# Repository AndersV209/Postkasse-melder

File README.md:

# Postkasse melder

min version af postkasse melder 

der sidder 2 stk micro switch i postkassen, en på den øverste låge og en på den nederste låge, så den selv resetter når postkassen er tømt.

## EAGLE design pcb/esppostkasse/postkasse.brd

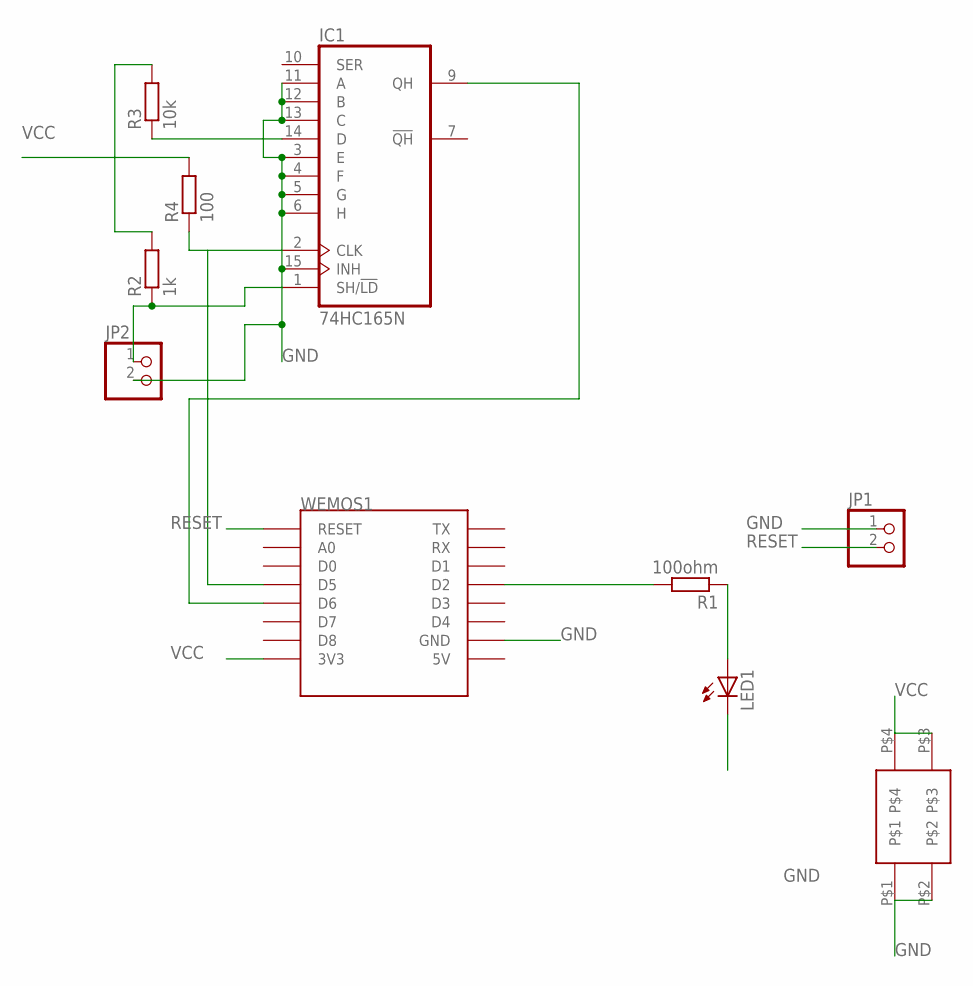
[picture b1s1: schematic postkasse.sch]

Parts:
IC1: 74HC165N; DIL16
JP1, JP2: PINHD-1X2; 1X02
LED1: LED5MM
R1: 100ohm; 0204/7
R2: 1k; 0204/7
R3: 10k; 0204/7
R4: 100; 0204/7
U$1: BAT18650
WEMOS1: WEMOS-D1-MINI

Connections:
GND: IC1.3 (E), IC1.4 (F), IC1.5 (G), IC1.6 (H), IC1.8 (GND), IC1.11 (A), IC1.12 (B), IC1.13 (C), IC1.15 (INH), JP1.1, JP2.2, LED1.K (C), U$1.P$1, U$1.P$2, WEMOS1.GND
unnamed: LED1.A, R1.1
unnamed: R1.2, WEMOS1.D2
unnamed: IC1.1 (SH/!LD), JP2.1, R2.1
unnamed: IC1.2 (CLK), R4.1, WEMOS1.D5
unnamed: IC1.14 (D), R3.1
unnamed: IC1.9 (QH), WEMOS1.D6
RESET: JP1.2, WEMOS1.RESET
VCC: IC1.16 (VCC), R2.2, R3.2, R4.2, U$1.P$3, U$1.P$4, WEMOS1.3V3

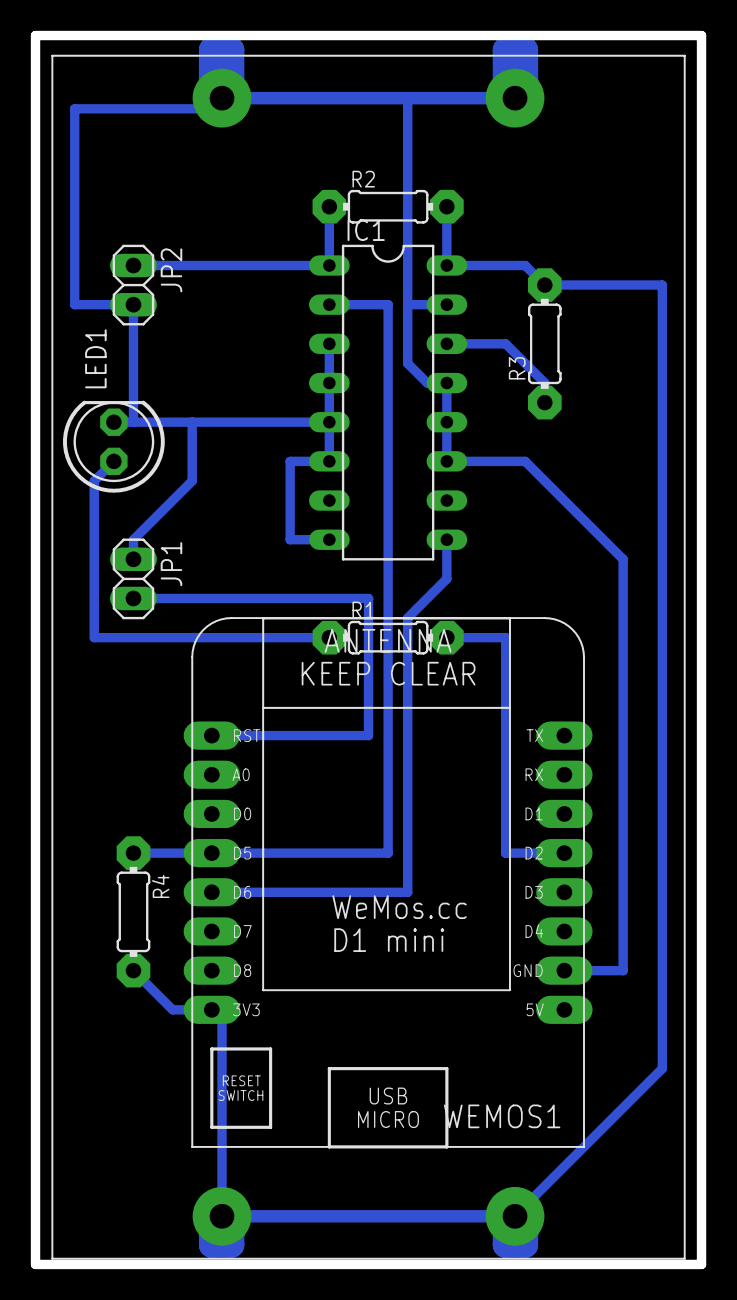
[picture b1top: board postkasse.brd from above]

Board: 2 copper layers, 43.2 x 79.7 mm, 10 parts (0 on the bottom side), 9 nets.
